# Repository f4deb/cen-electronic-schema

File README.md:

cen-electronic-schema
=====================

Schema of all electronical boards of Cybernetique en Nord

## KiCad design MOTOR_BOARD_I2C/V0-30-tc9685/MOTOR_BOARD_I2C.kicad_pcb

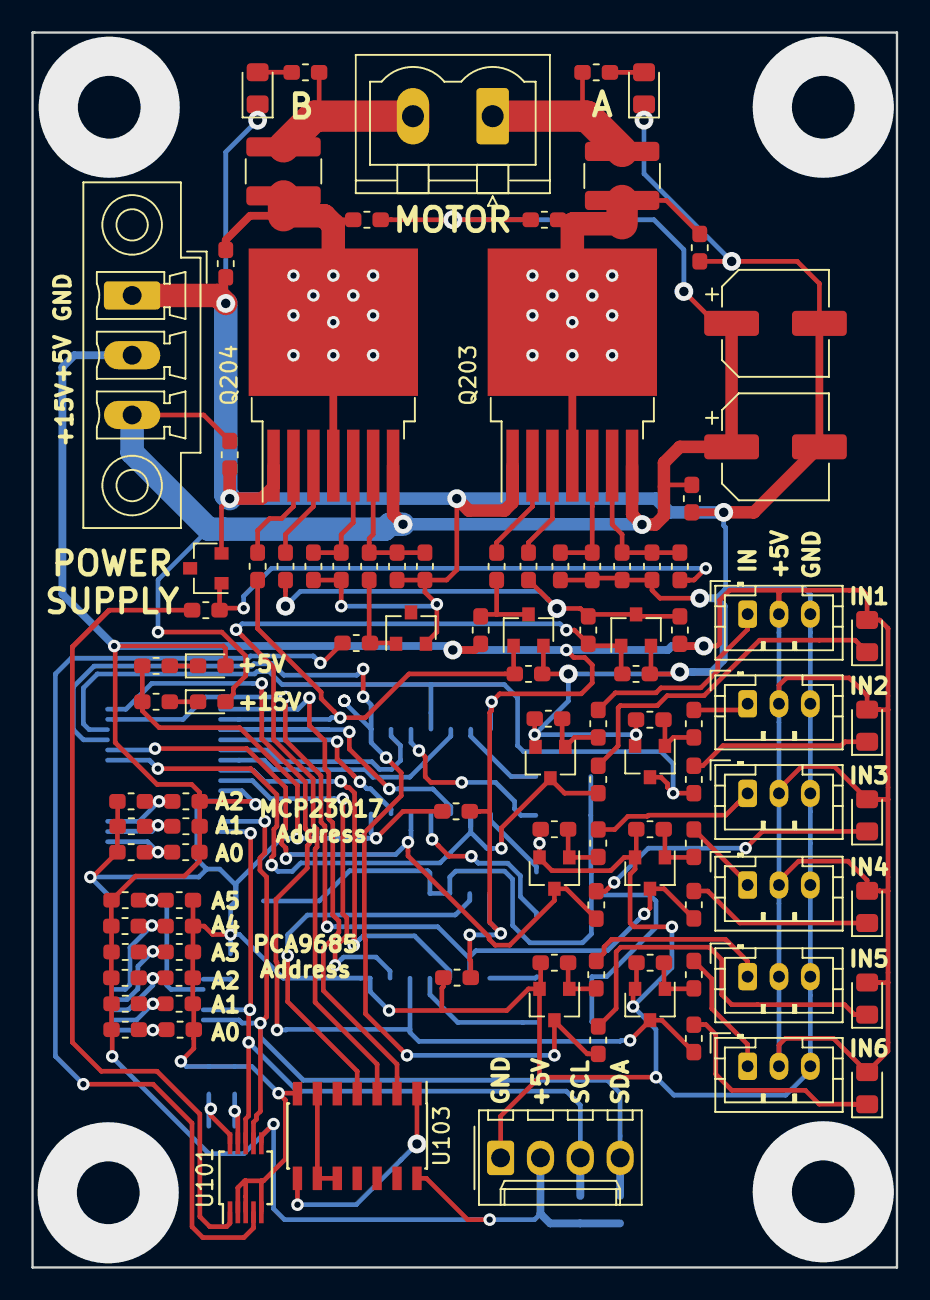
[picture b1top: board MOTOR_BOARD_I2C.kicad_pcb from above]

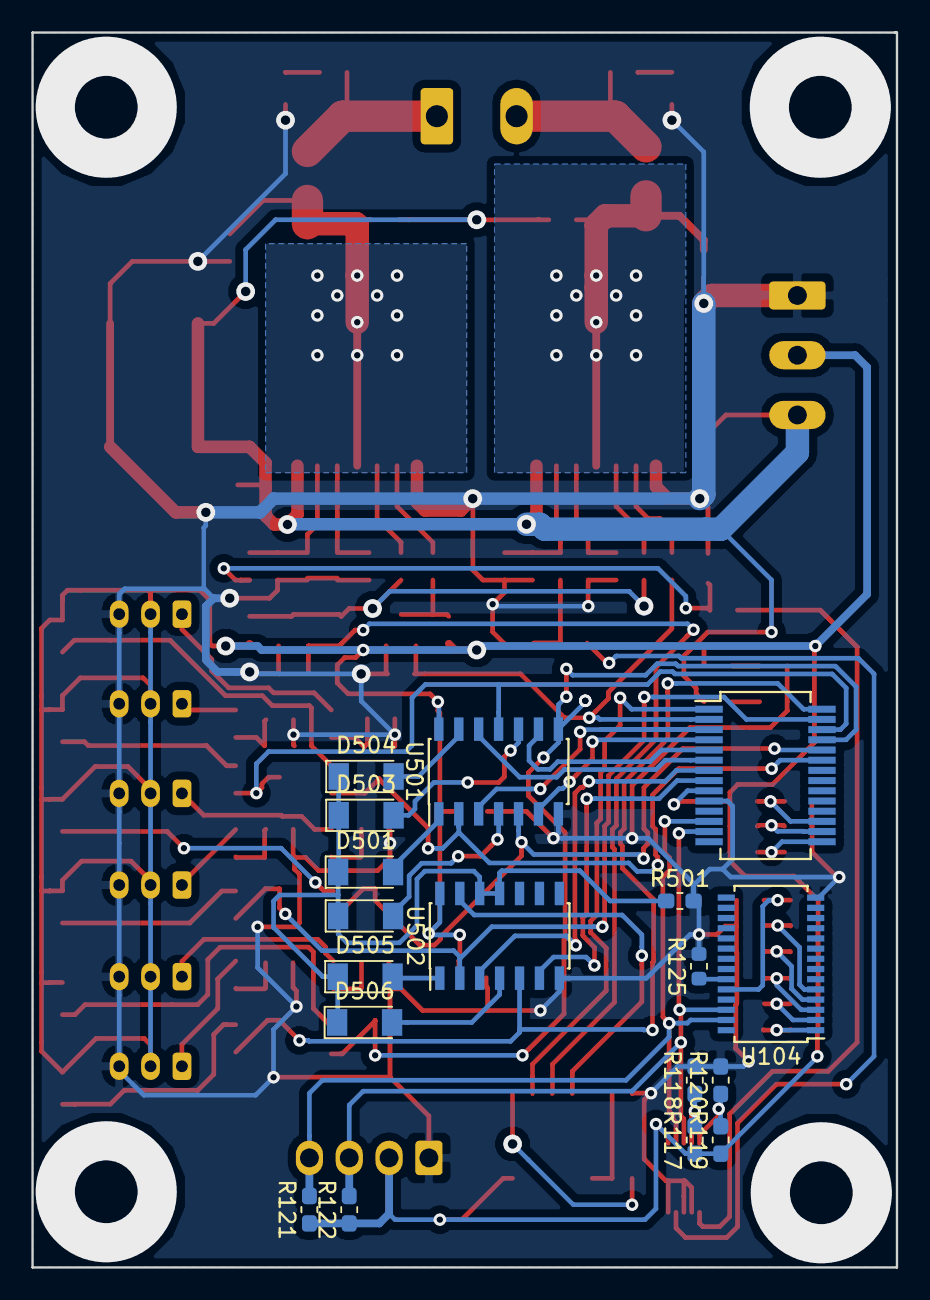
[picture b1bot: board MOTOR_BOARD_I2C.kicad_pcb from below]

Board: 2 copper layers, 55.1 x 78.7 mm, 124 parts (18 on the bottom side), 82 nets.

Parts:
C201, C202, C211, C212: C; C_0603_1608Metric_Pad1.05x0.95mm_HandSolder
C203, C210, C501, C502: 100n; C_0603_1608Metric_Pad1.05x0.95mm_HandSolder
C204, C209: 1000µ; CP_Elec_6.3x5.4
C205, C206, C207, C208: 220n; C_0603_1608Metric_Pad1.05x0.95mm_HandSolder
D101, D102: Vert; LED_0603_1608Metric_Pad1.05x0.95mm_HandSolder
D201, D204: D_Zener_Small_ALT; SOT-23
D202, D203, D401, D402, D403, D404, D405, D406: LED; LED_0805_2012Metric_Pad1.15x1.40mm_HandSolder
D501, D502, D503, D504, D505, D506: B140-E3; D_MiniMELF
J1: Conn_01x02; PhoenixContact_MSTBVA_2,5_2-G-5,08_1x02_P5.08mm_Vertical
J101: Conn_01x03; PhoenixContact_MCV_1,5_3-GF-3.81_1x03_P3.81mm_Vertical_Thre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
J102: Conn_01x04; Molex_KK-254_AE-6410-04A_1x04_P2.54mm_Vertical
J401, J402, J403, J404, J405, J406: Conn_01x03_Male; JST_PH_B3B-PH-K_1x03_P2.00mm_Vertical
Q201, Q202, Q401, Q402, Q403, Q404, Q405, Q406: 2N7002; SOT-23
Q203, Q204: BTN8982TA; TO-263-7_TabPin8
R101, R103, R105, R107, R109, R111, R113, R115, R117, R119, R123: 0; R_0603_1608Metric_Pad1.05x0.95mm_HandSolder
R102, R104, R106, R108, R110, R112, R114, R116, R118, R120, R121, R122, R124, R203, R205, R209, R210, R215, R216, R501: 10k; R_0603_1608Metric_Pad1.05x0.95mm_HandSolder
R125: 0; R_0603_1608Metric
R126, R405, R406, R411, R412, R417, R418: 1k; R_0603_1608Metric_Pad1.05x0.95mm_HandSolder
R127: 3.3k; R_0603_1608Metric_Pad1.05x0.95mm_HandSolder
R201, R204, R403, R404, R409, R410, R415, R416: 100k; R_0603_1608Metric_Pad1.05x0.95mm_HandSolder
R202: NC-0; R_0603_1608Metric_Pad1.05x0.95mm_HandSolder
R206, R207, R208, R211, R212, R213, R214, R217, R218, R219: R; R_0603_1608Metric_Pad1.05x0.95mm_HandSolder
R401, R402, R407, R408, R413, R414: 100; R_0603_1608Metric_Pad1.05x0.95mm_HandSolder
TH201, TH202: Thermistor; R_1218_3246Metric_Pad1.22x4.75mm_HandSolder
U101: MCP3427-xUN; MSOP-10_3x3mm_P0.5mm
U102: MCP23017_SS; SSOP-28_5.3x10.2mm_P0.65mm
U103: 74HC00; SOIC-14_3.9x8.7mm_P1.27mm
U104: PCA9685PW; TSSOP-28_4.4x9.7mm_P0.65mm
U501, U502: 74HC02; SOIC-14_3.9x8.7mm_P1.27mm

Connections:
+5VD: C501.1, C502.1, D101.2, D401.2, D402.2, D403.2, D404.2, D405.2, D406.2, J101.2, J102.2, J401.2, J402.2, J403.2, J404.2, J405.2, J406.2, R101.1, R103.1, R105.1, R107.1, R109.1, R111.1, R113.1, R115.1, R117.1, R119.1, R121.1, R122.1, R123.1, R203.1, R205.1, U101.6, U102.9, U103.14, U501.14, U502.14
+15V: C203.1, C204.1, C205.1, C207.1, C209.1, C210.1, D102.2, J101.3, Q203.7, Q204.7
/IN0: Q401.3, R405.2, U102.23, U501.2
/IN1: Q403.3, R411.2, U102.24, U501.5
/IN2: Q405.3, R417.2, U102.25, U501.8
/IN3: Q402.3, R406.2, U102.26, U501.11
/IN4: Q404.3, R412.2, U102.27, U502.2
/IN5: Q406.3, R418.2, U102.28, U502.5
/IS1: R206.1, U101.1
/IS2: R219.1, U101.4
/M1A: J1.1, R212.2, TH201.1
/M1B: J1.2, R213.2, TH202.1
/RSTIN0: U102.3, U501.3
/RSTIN1: U102.4, U501.6
/RSTIN2: U102.5, U501.9
/RSTIN3: U102.6, U501.12
/RSTIN4: U102.7, U502.3
/RSTIN5: U102.8, U502.6
/SCL: J102.3, R122.2, U101.8, U102.13, U104.26
/SDA: J102.4, R121.2, U101.7, U102.12, U104.27
/STOPMOTOR: U103.4, U502.13
/Sheet5DBEC701/S0: D501.2, U501.1
/Sheet5DBEC701/S1: D502.2, U501.4
/Sheet5DBEC701/S2: D503.2, U501.10
/Sheet5DBEC701/S3: D504.2, U501.13
/Sheet5DBEC701/S4: D505.2, U502.1
/Sheet5DBEC701/S5: D506.2, U502.4
/Sheet5DC0EE77/DIR1: Q202.1, R204.1, R216.1, U102.2
/Sheet5DC0EE77/PWM1: Q201.1, R201.1, R202.2, U103.3
GND: C201.2, C202.2, C203.2, C204.2, C206.2, C208.2, C209.2, C210.2, C211.2, C212.2, C501.2, C502.2, D201.2, D202.1, D203.1, D204.2, J101.1, J102.1, J401.3, J402.3, J403.3, J404.3, J405.3, J406.3, Q201.2, Q202.2, Q203.1, Q204.1, Q401.2, Q402.2, Q403.2, Q404.2, Q405.2, Q406.2, R102.2, R104.2, R106.2, R108.2, R110.2, R112.2, R114.2, R116.2, R118.2, R120.2, R124.2, R125.2, R126.2, R127.2, R201.2, R204.2, R208.2, R211.2, R214.2, R217.2, R403.2, R404.2, R409.2, R410.2, R415.2, R416.2, R501.2, U101.2, U101.3, U101.5, U102.10, U103.7, U104.14, U501.7, U502.7
unnamed: C201.1, Q203.6, R207.2, R208.1
unnamed: C202.1, Q203.5, R211.1
unnamed: C205.2, C206.1, Q203.4, Q203.8, TH201.2
unnamed: C207.2, C208.1, Q204.4, Q204.8, TH202.2
unnamed: C211.1, Q204.5, R214.1
unnamed: C212.1, Q204.6, R217.1, R218.2
unnamed: D101.1, R126.1
unnamed: D102.1, R127.1
unnamed: D201.1, R206.2, R207.1
unnamed: D202.2, R212.1
unnamed: D203.2, R213.1
unnamed: D204.1, R218.1, R219.2
unnamed: D401.1, R405.1
unnamed: D402.1, R406.1
unnamed: D403.1, R411.1
unnamed: D404.1, R412.1
unnamed: D405.1, R417.1
unnamed: D406.1, R418.1
unnamed: D501.1, D502.1, D503.1, D504.1, D505.1, D506.1, R501.1, U502.11, U502.12
unnamed: J401.1, R401.2
unnamed: J402.1, R402.2
unnamed: J403.1, R407.2
unnamed: J404.1, R408.2
unnamed: J405.1, R413.2
unnamed: J406.1, R414.2
unnamed: Q201.3, R202.1, R203.2, R209.2, R215.1
unnamed: Q202.3, R205.2, R210.2
unnamed: Q203.2, R210.1
unnamed: Q203.3, R209.1
unnamed: Q204.2, R216.2
unnamed: Q204.3, R215.2
unnamed: Q401.1, R401.1, R403.1
unnamed: Q402.1, R402.1, R404.1
unnamed: Q403.1, R407.1, R409.1
unnamed: Q404.1, R408.1, R410.1
unnamed: Q405.1, R413.1, R415.1
unnamed: Q406.1, R414.1, R416.1
unnamed: R101.2, R102.1, U104.1
unnamed: R103.2, R104.1, U102.17
unnamed: R105.2, R106.1, U104.2
unnamed: R107.2, R108.1, U102.16
unnamed: R109.2, R110.1, U104.3
unnamed: R111.2, R112.1, U102.15
unnamed: R113.2, R114.1, U104.4
unnamed: R115.2, R116.1, U104.5
unnamed: R117.2, R118.1, U101.9
unnamed: R119.2, R120.1, U101.10
unnamed: R123.2, R124.1, U104.24
unnamed: R125.1, U104.23
unnamed: U102.1, U103.2
unnamed: U103.1, U103.8
unnamed: U103.6, U103.9, U103.10

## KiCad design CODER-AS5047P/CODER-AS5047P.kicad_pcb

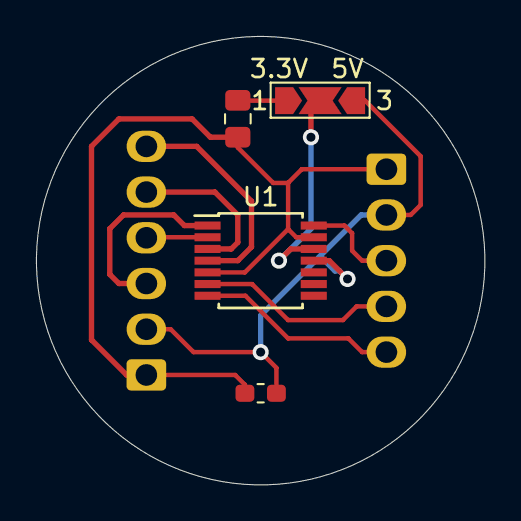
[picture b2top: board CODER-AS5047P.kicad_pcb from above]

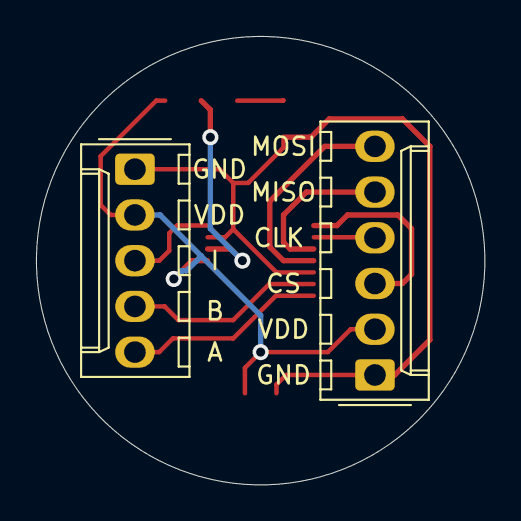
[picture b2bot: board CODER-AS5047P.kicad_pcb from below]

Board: 2 copper layers, 24.9 x 24.9 mm, 6 parts (2 on the bottom side), 11 nets.

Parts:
C1: 1µ/10V; C_0805_2012Metric_Pad1.15x1.40mm_HandSolder
C2: 10n; C_0603_1608Metric_Pad1.05x0.95mm_HandSolder
J1: Conn_01x05; Molex_KK-254_AE-6410-05A_1x05_P2.54mm_Vertical
J2: Conn_01x06; Molex_KK-254_AE-6410-06A_1x06_P2.54mm_Vertical
JP1: SolderJumper_3_Open; SolderJumper-3_P2.0mm_Open_TrianglePad1.0x1.5mm_NumberLabels
U1: AS5047P; TSSOP-14_4.4x5mm_P0.65mm

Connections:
GND: C1.2, C2.1, J1.1, J2.1, U1.5, U1.13
unnamed: C1.1, JP1.1
unnamed: J1.3, U1.14
unnamed: J1.4, U1.6
unnamed: J1.5, U1.7
unnamed: J2.3, U1.1
unnamed: J2.4, U1.2
unnamed: J2.5, U1.3
unnamed: J2.6, U1.4
unnamed: JP1.2, U1.12
VDD: C2.2, J1.2, J2.2, JP1.3, U1.11

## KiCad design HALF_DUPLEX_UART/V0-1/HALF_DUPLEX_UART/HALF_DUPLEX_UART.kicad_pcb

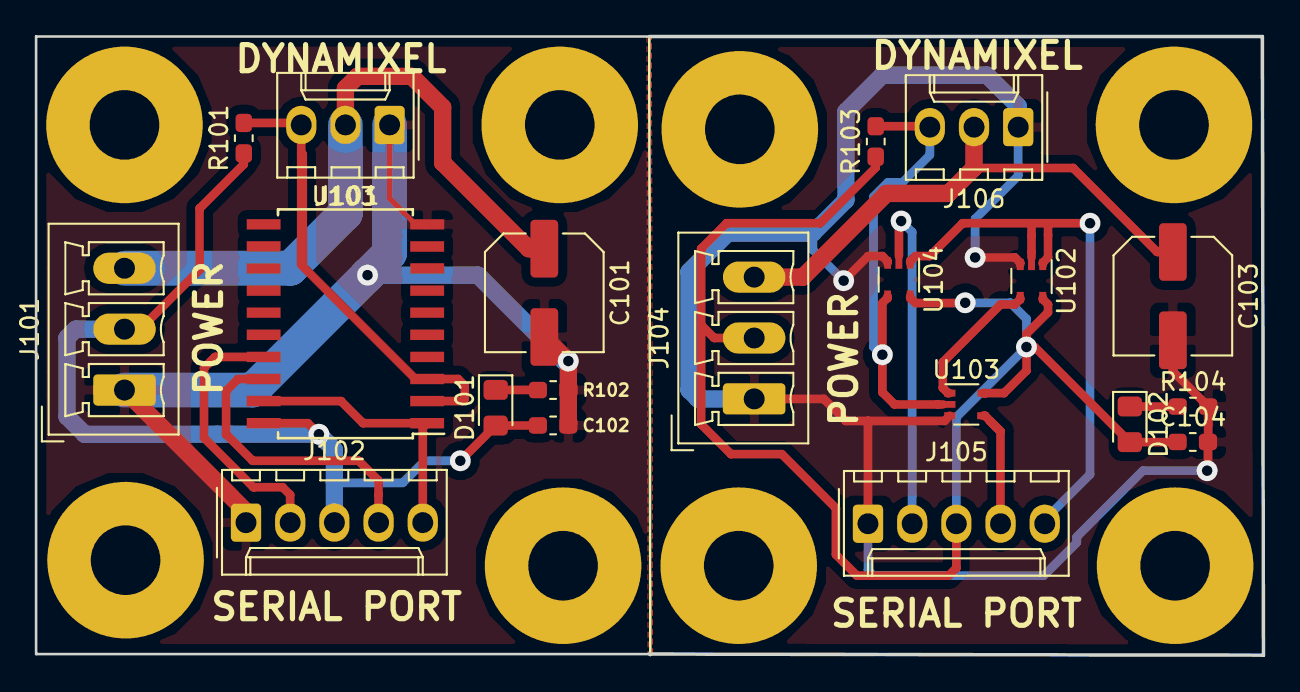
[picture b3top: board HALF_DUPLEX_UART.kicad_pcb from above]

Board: 2 copper layers, 70.5 x 35.6 mm, 20 parts (0 on the bottom side), 17 nets.

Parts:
C101, C103: 220µ; C_Elec_6.3x7.7
C102, C104: 100n; C_0603_1608Metric_Pad1.05x0.95mm_HandSolder
D101, D102: Vert; LED_0805_2012Metric_Pad1.15x1.40mm_HandSolder
J101, J104: Conn_01x03_Male; PhoenixContact_MCV_1,5_3-G-3.5_1x03_P3.50mm_Vertical
J102, J105: Conn_01x05_Male; Molex_KK-254_AE-6410-05A_1x05_P2.54mm_Vertical
J103, J106: Conn_01x03_Male; Molex_KK-254_AE-6410-03A_1x03_P2.54mm_Vertical
R101, R103: 10k; R_0603_1608Metric_Pad1.05x0.95mm_HandSolder
R102, R104: 1k; R_0603_1608Metric_Pad1.05x0.95mm_HandSolder
U101: 74LS241; SOIC-20W_7.5x12.8mm_P1.27mm
U102: 74LVC1G00; SOT-353_SC-70-5
U103, U104: 74AHC1G126; SOT-353_SC-70-5

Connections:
+5VA: C102.1, D101.2, J101.2, J102.3, R101.1, U101.20
+12V: C101.1, J101.3, J103.2
/DIR126: J105.5, U102.1, U102.2, U104.1
/DIR241: J102.5, U101.1, U101.19
/RX126: J105.4, U103.4
/RX241: J102.4, U101.18
/TX126: J105.2, U104.2
/TX241: J102.2, U101.17
GND: C103.2, C104.2, J104.1, J105.1, J106.1, R104.2, U102.3, U103.3, U104.3
GNDA: C101.2, C102.2, J101.1, J102.1, J103.1, R102.2, U101.10
unnamed: D101.1, R102.1
unnamed: D102.1, R104.1
unnamed: J103.3, R101.2, U101.2, U101.3
unnamed: J106.3, R103.2, U103.2, U104.4
unnamed: U102.4, U103.1
VCC: C104.1, D102.2, J104.2, J105.3, R103.1, U102.5, U103.5, U104.5
VDD: C103.1, J104.3, J106.2

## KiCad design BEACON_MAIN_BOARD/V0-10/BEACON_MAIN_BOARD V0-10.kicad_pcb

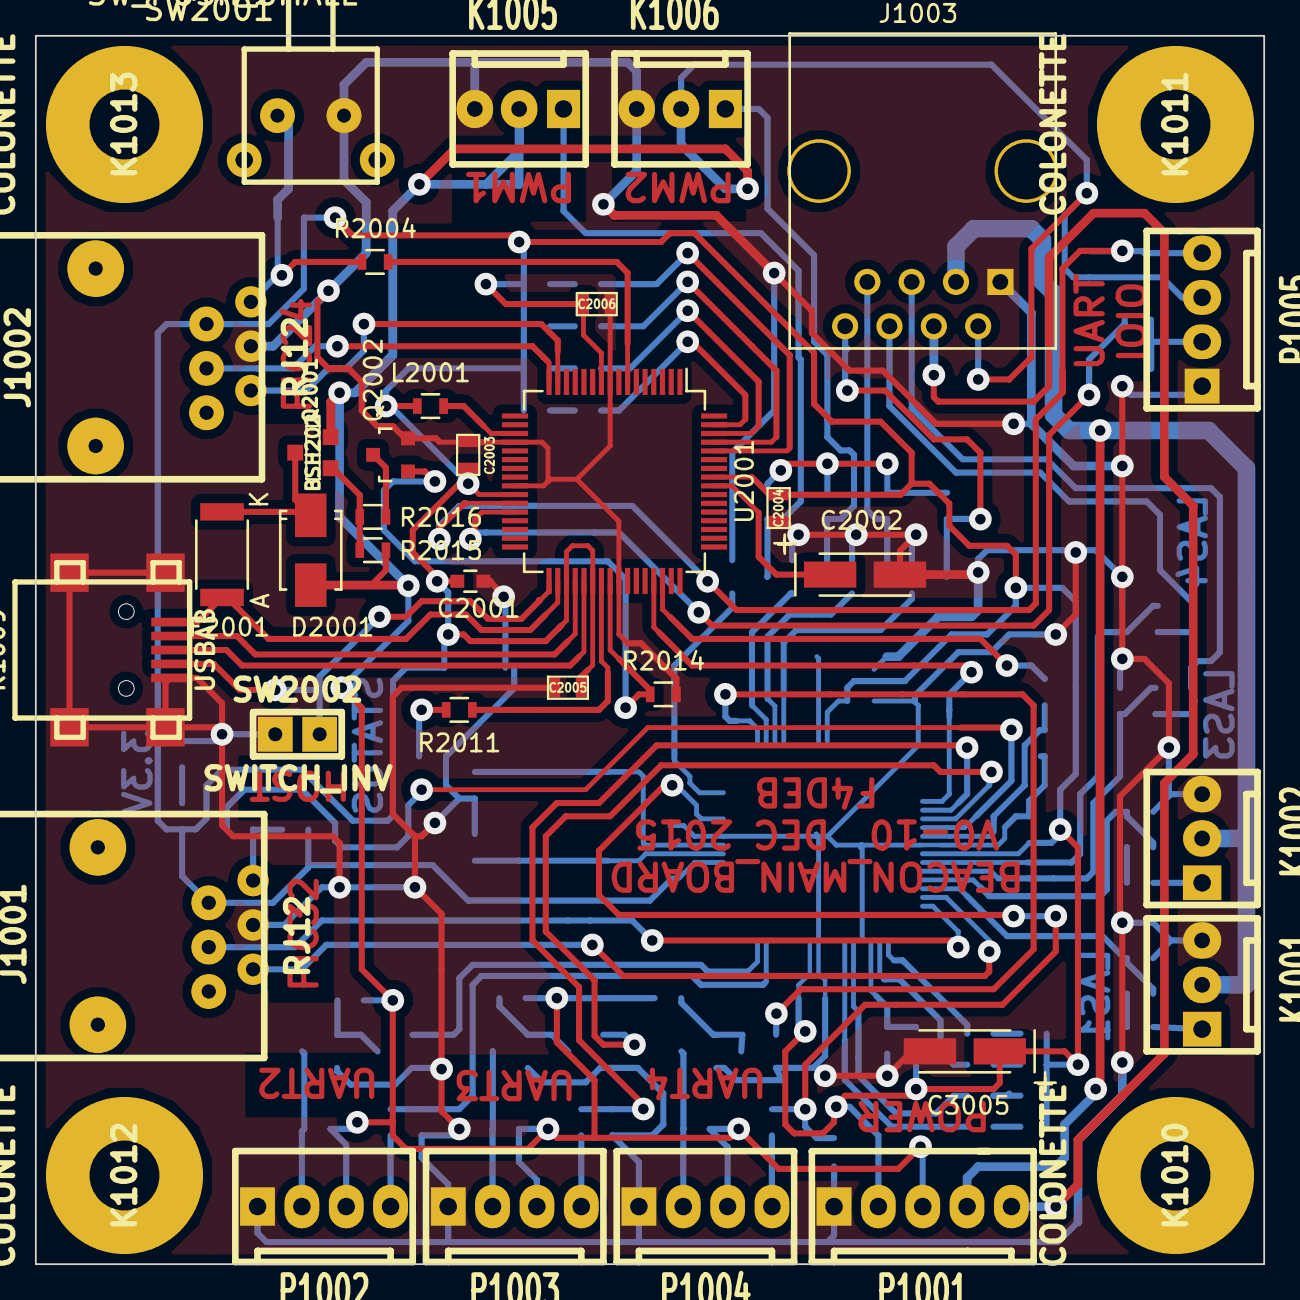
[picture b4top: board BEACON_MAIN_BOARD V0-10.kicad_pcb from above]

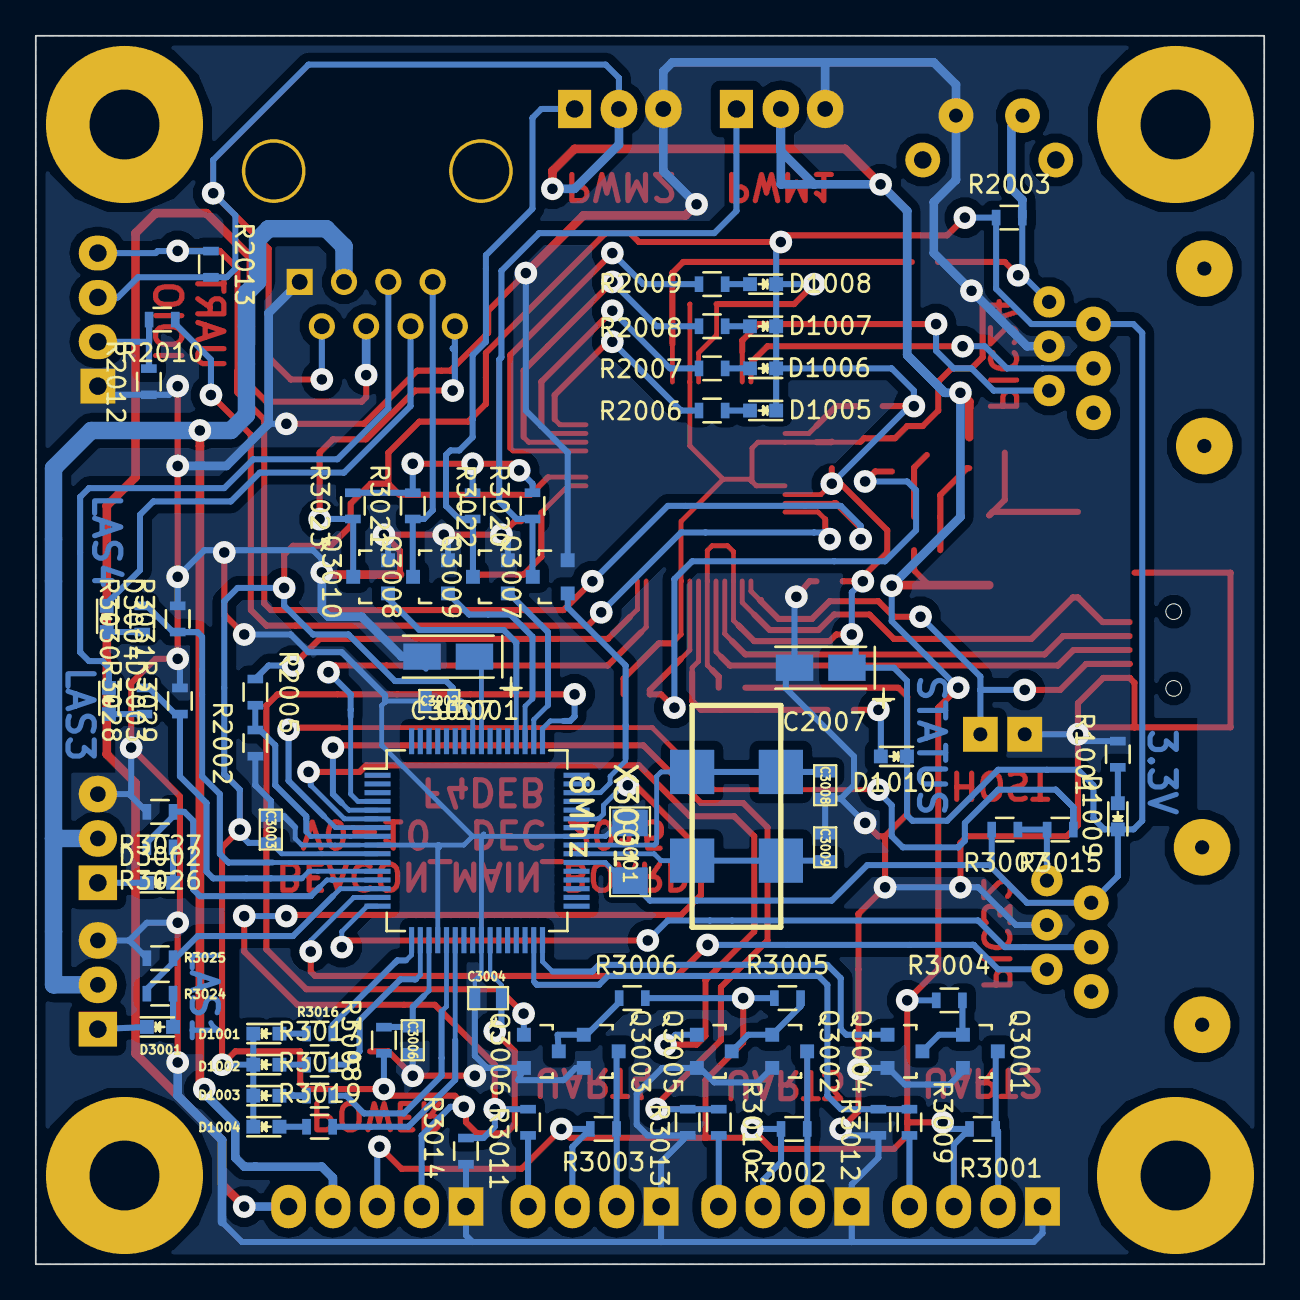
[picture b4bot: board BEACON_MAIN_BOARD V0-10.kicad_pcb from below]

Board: 2 copper layers, 70.4 x 70.4 mm, 114 parts (77 on the bottom side), 88 nets.

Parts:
C2001: 100n; C_0603
C2002: 10U/10V; TantalC_SizeA_EIA-3216_HandSoldering
C2003, C2004, C2005, C2006, C3002, C3003, C3004, C3006: 100n; SM0603_Capa
C2007: 10U/10V; TantalC_SizeA_EIA-3216_Wave
C3001: 100n; SM1206
C3005: 10u/10V; TantalC_SizeA_EIA-3216_HandSoldering
C3007: 10u/10V; TantalC_SizeA_EIA-3216_Wave
C3008, C3009: 22p; SM0603_Capa
D1001, D1005: BLEU; LED-0603
D1002, D1006: ROUGE; LED-0603
D1003, D1007, D3001, D3002, D3003, D3004: JAUNE; LED-0603
D1004, D1008, D1009, D1010: VERT; LED-0603
D2001: B340A; SMA_Standard
F2001: FUSE; R_2010
J1001, J1002: RJ12
J1003: RJ45; RJ45_8
K1001, K1002, K1005, K1006: CONN_3; KK-3
K1009: USBAB; conn_usb_B_mini_smd
K1010, K1011, K1012, K1013: COLONETTE
L2001: 30Ohms; R_0603
P1001: CONN_5; KK-5
P1002, P1003, P1004, P1005: CONN_4; KK-4
Q2001: BSH202; SOT23GDS
Q2002, Q3001, Q3002, Q3003, Q3004, Q3005, Q3006, Q3007, Q3008, Q3009, Q3010: 2N7002; SOT-23
R1001, R3016, R3017, R3018, R3019: 680; R_0603
R2002, R2012, R3012, R3013, R3014: 22k; R_0603
R2003, R3001, R3002, R3003, R3004, R3005, R3006, R3007, R3020, R3021, R3022, R3023: 10k; R_0603
R2004, R3015: 470; R_0603
R2005, R2010, R3009, R3010, R3011: 12k; R_0603
R2006, R2007, R2008, R2009, R2011, R3024, R3025, R3026, R3027, R3028, R3029, R3030, R3031: 1.5k; R_0603
R2013: 4.7k; R_0603
R2014: 100k; R_0603
R2015: 8.2k; R_0603
R2016: 2.2k; R_0603
R3008: 0; R_0603
SW2001: SW_PUSH_SMALL; SW
SW2002: SWITCH_INV; CAVALIER
U2001: PIC24FJ256GB206; TQFP-64_10x10mm_Pitch0.5mm
U3001: PIC32MX795F512H; TQFP-64_10x10mm_Pitch0.5mm
X3001: 8Mhz; QTZ

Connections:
+3V3: C2001.1, C2003.1, C2004.1, C2005.1, C2006.1, C2007.1, C3001.1, C3002.1, C3003.1, C3004.1, C3005.1, D1001.1, D1002.1, D1003.1, D1004.1, D1005.1, D1006.1, D1007.1, D1008.1, D1009.1, D1010.1, J1001.2, J1002.2, L2001.1, P1001.2, R2003.1, R3007.2, R3008.1, U2001.10, U2001.26, U2001.35, U2001.38, U2001.57, U3001.10, U3001.26, U3001.38, U3001.57
+5V: R3020.2, R3021.2, R3022.2, R3023.2
+5VD: D2001.2, J1003.2, K1005.2, K1006.2, P1001.3, P1002.3, P1003.3, P1004.3, P1005.3, Q2001.S, R2013.2, R2015.2, R3001.2, R3002.2, R3003.2, R3004.1, R3005.1, R3006.1
+12V: J1003.3, K1001.2, K1002.2, P1001.4
+BATT: J1003.4, P1001.5
/IOIO/BLEU24: D1005.2, R2006.2
/IOIO/D+: K1009.3, U2001.37
/IOIO/D-: K1009.2, U2001.36
/IOIO/HOST: Q2002.1, R2014.1, U2001.40
/IOIO/JAUNE24: D1007.2, R2008.2
/IOIO/PGC24: J1002.5, U2001.15
/IOIO/PGD24: J1002.4, U2001.16
/IOIO/ROUGE24: D1006.2, R2007.2
/IOIO/RST24: J1002.1, R2003.2, R2004.1, SW2001.1
/IOIO/RX124: U2001.45, U3001.4
/IOIO/RX424: P1005.4, R2013.1, U2001.27
/IOIO/STATUS24: D1010.2, R2011.2
/IOIO/TX1: R2005.1, U2001.46
/IOIO/TX4: R2010.1, U2001.28
/IOIO/TX424: P1005.2, R2010.2, R2012.2
/IOIO/USBID: K1009.4, SW2002.2, U2001.33
/IOIO/VBUS: F2001.1, K1009.1, U2001.34
/IOIO/VERT24: D1008.2, R2009.2
/PIC32MX795F512H/BLEU32: D1001.2, R3016.1
/PIC32MX795F512H/JAUNE32: D1003.2, R3018.1
/PIC32MX795F512H/LASER1: D3001.1, K1001.1
/PIC32MX795F512H/LASER2: D3002.1, K1002.1
/PIC32MX795F512H/LASER3: D3003.1, J1003.5
/PIC32MX795F512H/LASER4: D3004.1, J1003.6
/PIC32MX795F512H/OC1: Q3007.1, U3001.46
/PIC32MX795F512H/OC1-5V: K1005.1, Q3007.3, R3020.1
/PIC32MX795F512H/OC3: Q3009.1, U3001.50
/PIC32MX795F512H/OC3-5V: K1006.1, Q3009.3, R3022.1
/PIC32MX795F512H/OC4: Q3008.1, U3001.51
/PIC32MX795F512H/OC4-5V: J1003.7, Q3008.3, R3021.1
/PIC32MX795F512H/OC5: Q3010.1, U3001.52
/PIC32MX795F512H/OC5-5V: J1003.8, Q3010.3, R3023.1
/PIC32MX795F512H/PGC32: J1001.5, U3001.15
/PIC32MX795F512H/PGD32: J1001.4, U3001.16
/PIC32MX795F512H/PIC32RST: J1001.1, R3007.1, R3015.2
/PIC32MX795F512H/ROUGE32: D1002.2, R3017.1
/PIC32MX795F512H/RX232: P1002.4, R3009.2
/PIC32MX795F512H/RX332: P1003.4, R3010.2
/PIC32MX795F512H/RX432: P1004.4, R3011.2
/PIC32MX795F512H/RX632: R2002.2, R2005.2, U3001.8
/PIC32MX795F512H/TX232: P1002.2, Q3001.3, R3001.1
/PIC32MX795F512H/TX332: P1003.2, Q3002.3, R3002.1
/PIC32MX795F512H/TX432: P1004.2, Q3003.3, R3003.1
/PIC32MX795F512H/VERT32: D1004.2, R3019.1
GND: C2001.2, C2002.2, C2003.2, C2004.2, C2005.2, C2006.2, C2007.2, C3001.2, C3002.2, C3003.2, C3004.2, C3005.2, C3006.2, C3007.2, C3008.2, C3009.2, J1001.3, J1002.3, J1003.1, K1001.3, K1002.3, K1005.3, K1006.3, K1009.5, P1001.1, P1002.1, P1003.1, P1004.1, P1005.1, Q2002.2, Q3001.2, Q3002.2, Q3003.2, Q3004.2, Q3005.2, Q3006.2, Q3007.2, Q3008.2, Q3009.2, Q3010.2, R1001.2, R2002.1, R2012.1, R2014.2, R3012.2, R3013.2, R3014.2, R3025.2, R3027.2, R3029.2, R3031.2, SW2001.2, SW2002.1, U2001.9, U2001.20, U2001.25, U2001.41, U3001.9, U3001.20, U3001.25, U3001.41
unnamed: C2002.1, U2001.56
unnamed: C3006.1, R3008.2, U3001.19
unnamed: C3007.1, U3001.56
unnamed: C3008.1, U3001.40, X3001.2
unnamed: C3009.1, U3001.39, X3001.1
unnamed: D1009.2, R1001.1
unnamed: D2001.1, F2001.2, Q2001.D
unnamed: D3001.2, R3024.1
unnamed: D3002.2, R3026.1
unnamed: D3003.2, R3028.1
unnamed: D3004.2, R3030.1
unnamed: L2001.2, U2001.19
unnamed: Q2001.G, R2015.1, R2016.1
unnamed: Q2002.3, R2016.2
unnamed: Q3001.1, Q3004.3, R3004.2
unnamed: Q3002.1, Q3005.3, R3005.2
unnamed: Q3003.1, Q3006.3, R3006.2
unnamed: Q3004.1, U3001.32
unnamed: Q3005.1, U3001.6
unnamed: Q3006.1, U3001.49
unnamed: R2004.2, U2001.7
unnamed: R2006.1, U2001.63
unnamed: R2007.1, U2001.62
unnamed: R2008.1, U2001.61
unnamed: R2009.1, U2001.60
unnamed: R2011.1, U2001.39
unnamed: R3009.1, R3012.1, U3001.31
unnamed: R3010.1, R3013.1, U3001.5
unnamed: R3011.1, R3014.1, U3001.43
unnamed: R3015.1, U3001.7
unnamed: R3016.2, U3001.17
unnamed: R3017.2, U3001.18
unnamed: R3018.2, U3001.21
unnamed: R3019.2, U3001.22
unnamed: R3024.2, R3025.1, U3001.14
unnamed: R3026.2, R3027.1, U3001.13
unnamed: R3028.2, R3029.1, U3001.12
unnamed: R3030.2, R3031.1, U3001.11

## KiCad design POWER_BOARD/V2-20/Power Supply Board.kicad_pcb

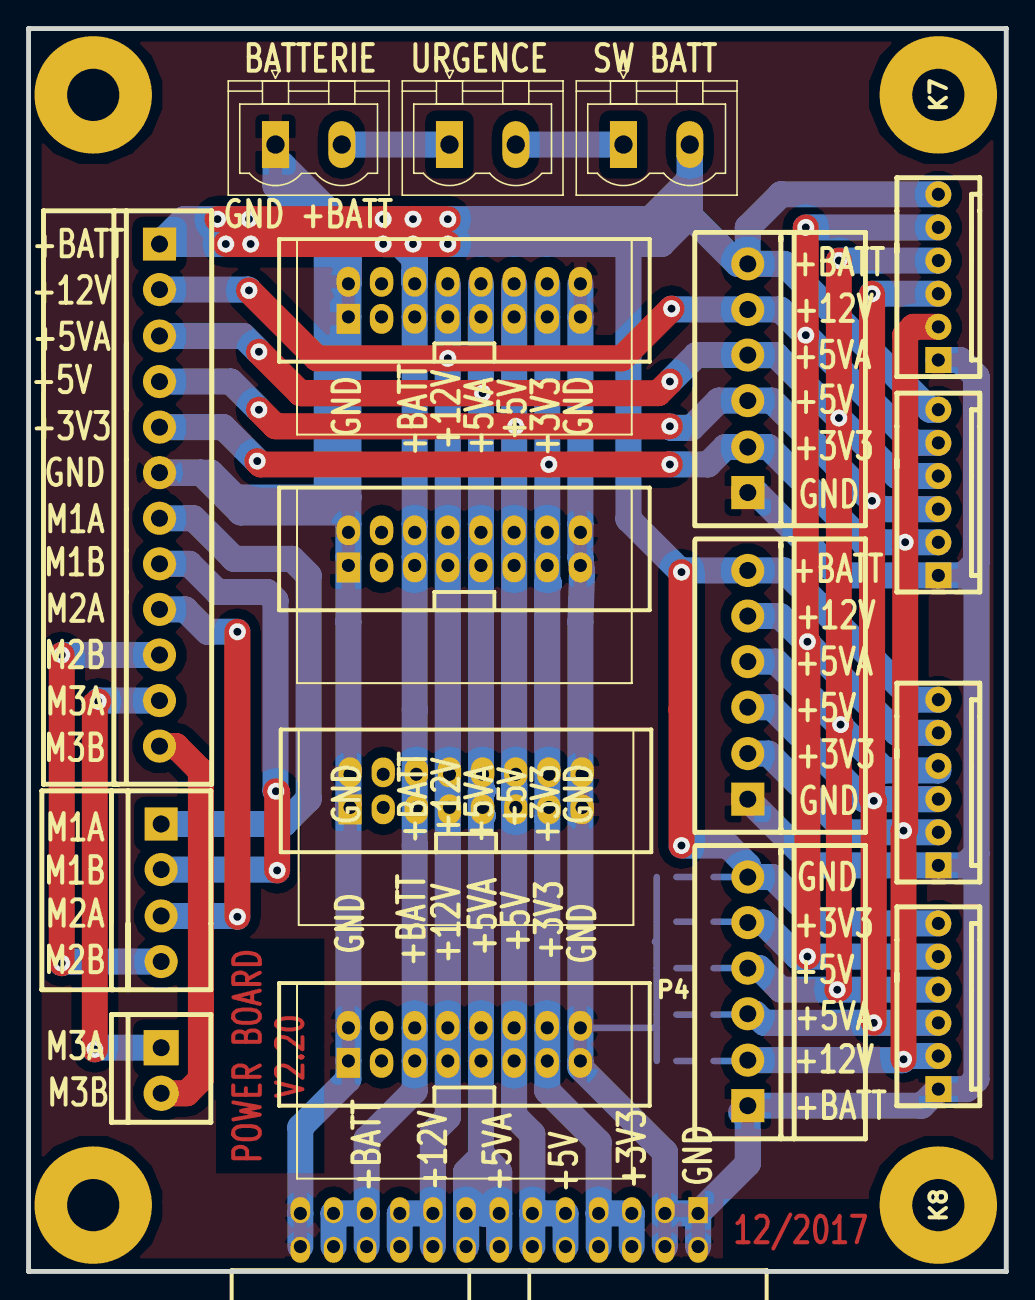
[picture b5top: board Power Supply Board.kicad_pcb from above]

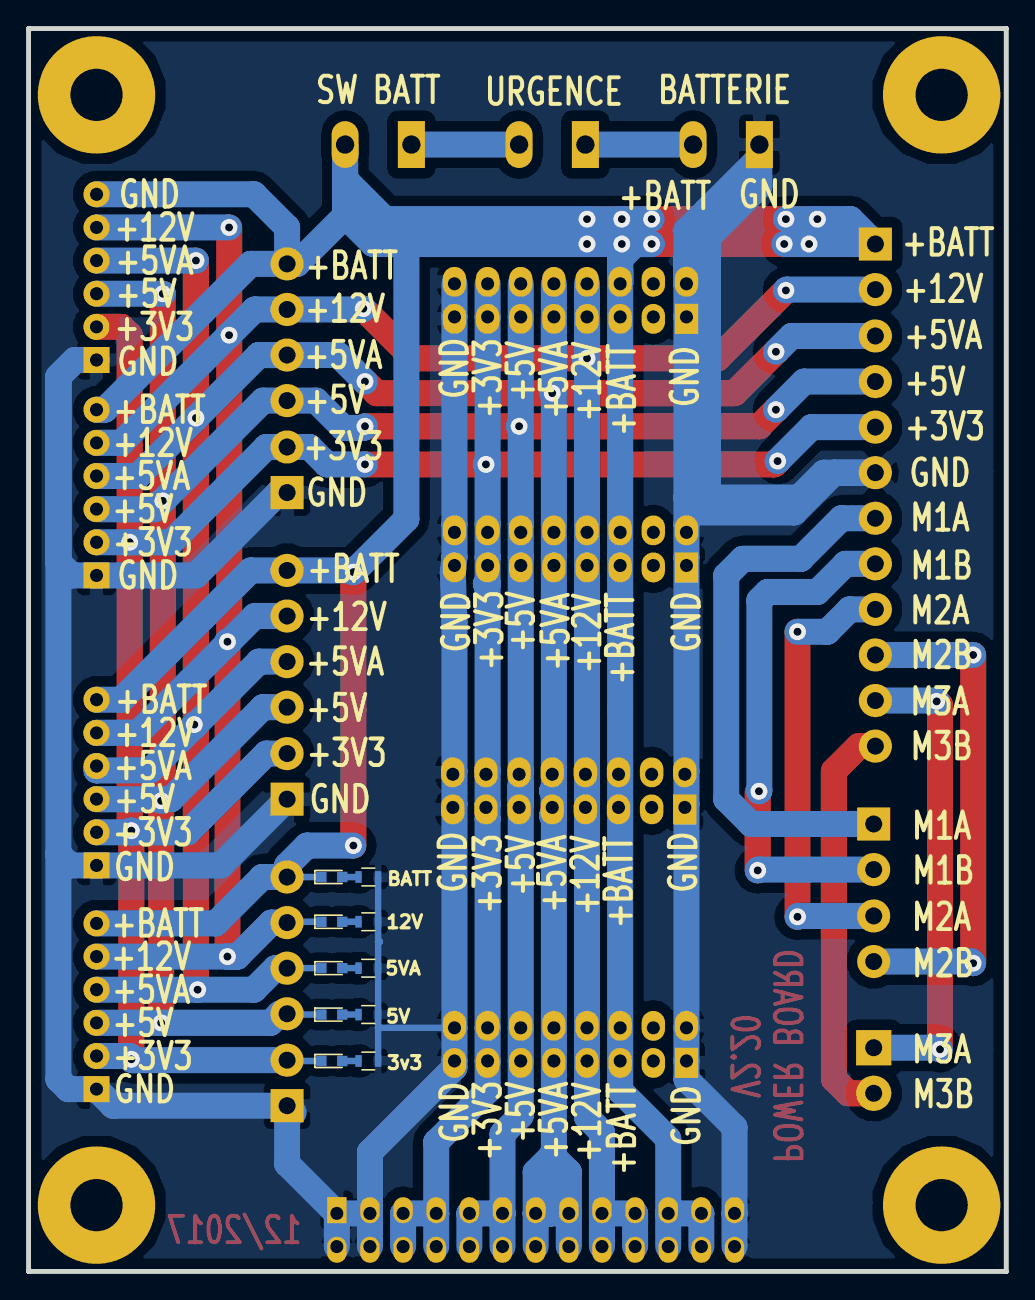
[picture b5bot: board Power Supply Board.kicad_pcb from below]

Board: 2 copper layers, 74.9 x 95.2 mm, 32 parts (10 on the bottom side), 19 nets.

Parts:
D10, D11, D12, D13, D14: LED; LED_0603
J1, J2, J3, J4: CONN_02X08; POWER_MODULE_0-20
J5: CONN_02X13; vasch_strip_13x2_90
K1, K2, K4: CONN_2; PhoenixContact_MSTBVA-G_02x5.08mm_Vertical
K3: CONN_2; WEIDMULLER-2
K5, K6, K7, K8: COLONETTE
P1: CONN_4; WEIDMULLER-4
P2: CONN_12; WEIDMULLER-12
P3, P4, P5: CONN_6; WEIDMULLER-6
P6, P7, P8, P9: CONN_6; KK-6
R5, R10: 3.3k; R_0603
R15, R20: 1k; R_0603
R21: 470; R_0603

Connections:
+3V3: D14.1, J1.13, J1.14, J2.13, J2.14, J3.13, J3.14, J4.13, J4.14, J5.5, J5.6, J5.7, J5.8, P2.5, P3.2, P4.2, P5.2, P6.2, P7.2, P8.2, P9.2
+5V: D13.1, J1.11, J1.12, J2.11, J2.12, J3.11, J3.12, J4.11, J4.12, J5.9, J5.10, J5.11, J5.12, P2.4, P3.3, P4.3, P5.3, P6.3, P7.3, P8.3, P9.3
+5VA: D12.1, J1.9, J1.10, J2.9, J2.10, J3.9, J3.10, J4.9, J4.10, J5.13, J5.14, J5.15, J5.16, P2.3, P3.4, P4.4, P5.4, P6.4, P7.4, P8.4, P9.4
+12V: D11.1, J1.7, J1.8, J2.7, J2.8, J3.7, J3.8, J4.7, J4.8, J5.17, J5.18, J5.19, J5.20, P2.2, P3.5, P4.5, P5.5, P6.5, P7.5, P8.5, P9.5
+BATT: D10.1, J1.5, J1.6, J2.5, J2.6, J3.5, J3.6, J4.5, J4.6, J5.21, J5.22, J5.23, J5.24, K4.2, P2.1, P3.6, P4.6, P5.6, P6.6, P7.6, P8.6, P9.6
/M1A: P1.1, P2.7
/M1B: P1.2, P2.8
/M2A: P1.3, P2.9
/M2B: P1.4, P2.10
/M3A: K3.1, P2.11
/M3B: K3.2, P2.12
GND: J1.1, J1.2, J1.15, J1.16, J2.1, J2.2, J2.15, J2.16, J3.1, J3.2, J3.15, J3.16, J4.1, J4.2, J4.15, J4.16, J5.1, J5.2, J5.3, J5.4, J5.25, J5.26, K1.1, P2.6, P3.1, P4.1, P5.1, P6.1, P7.1, P8.1, P9.1, R5.2, R10.2, R15.2, R20.2, R21.2
unnamed: D10.2, R5.1
unnamed: D11.2, R10.1
unnamed: D12.2, R15.1
unnamed: D13.2, R20.1
unnamed: D14.2, R21.1
unnamed: K1.2, K2.1
unnamed: K2.2, K4.1

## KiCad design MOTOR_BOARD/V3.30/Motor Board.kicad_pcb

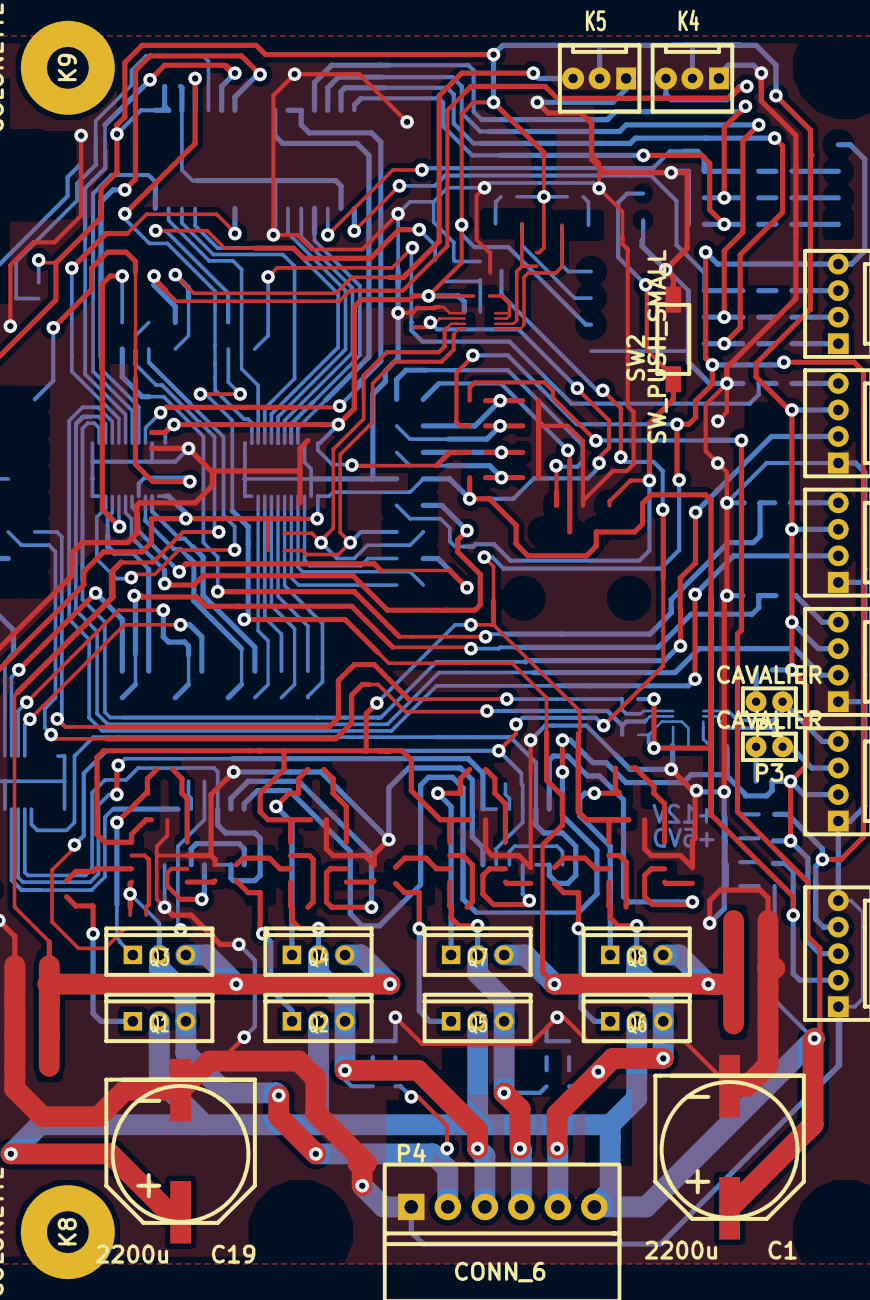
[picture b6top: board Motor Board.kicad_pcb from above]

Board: 2 copper layers, 24 parts (0 on the bottom side), 12 nets.

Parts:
C1, C19: 2200u; C_14x16
K2: CONN_4; KK-4
K4, K5: CONN_3; KK-3
K8, K9: COLONETTE
P1, P3: CAVALIER
P2, P5, P7, P8: CONN_4; KK-4
P4: CONN_6; WEIDMULLER-6
P6: CONN_5; KK-5
Q1, Q2, Q3, Q4, Q5, Q6, Q7, Q8: MOS_N; IRFIZ48V
SW2: SW_PUSH_SMALL; SW2

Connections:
+5VD: K4.2, K5.2, P2.2, P5.3, P6.3, P7.3, P8.3
+12V: K2.4, P6.4
+15V: C1.1, C19.1, P4.6, Q1.3, Q2.3, Q5.3, Q6.3
/MOTOR/ADC1: Q3.2, Q4.2
/MOTOR/ADC2: Q7.2, Q8.2
/MOTOR/M1A: P4.2, Q1.2, Q3.3
/MOTOR/M1B: P4.3, Q2.2, Q4.3
/MOTOR/M2A: P4.4, Q5.2, Q7.3
/MOTOR/M2B: P4.5, Q6.2, Q8.3
/PIC30F4013/SCL1: P2.3, P3.1
/PIC30F4013/SDA1: P1.1, P2.4
GND: C1.2, C19.2, K4.1, K5.1, P2.1, P4.1, P5.1, P6.1, P6.5, P7.1, P8.1, SW2.2
